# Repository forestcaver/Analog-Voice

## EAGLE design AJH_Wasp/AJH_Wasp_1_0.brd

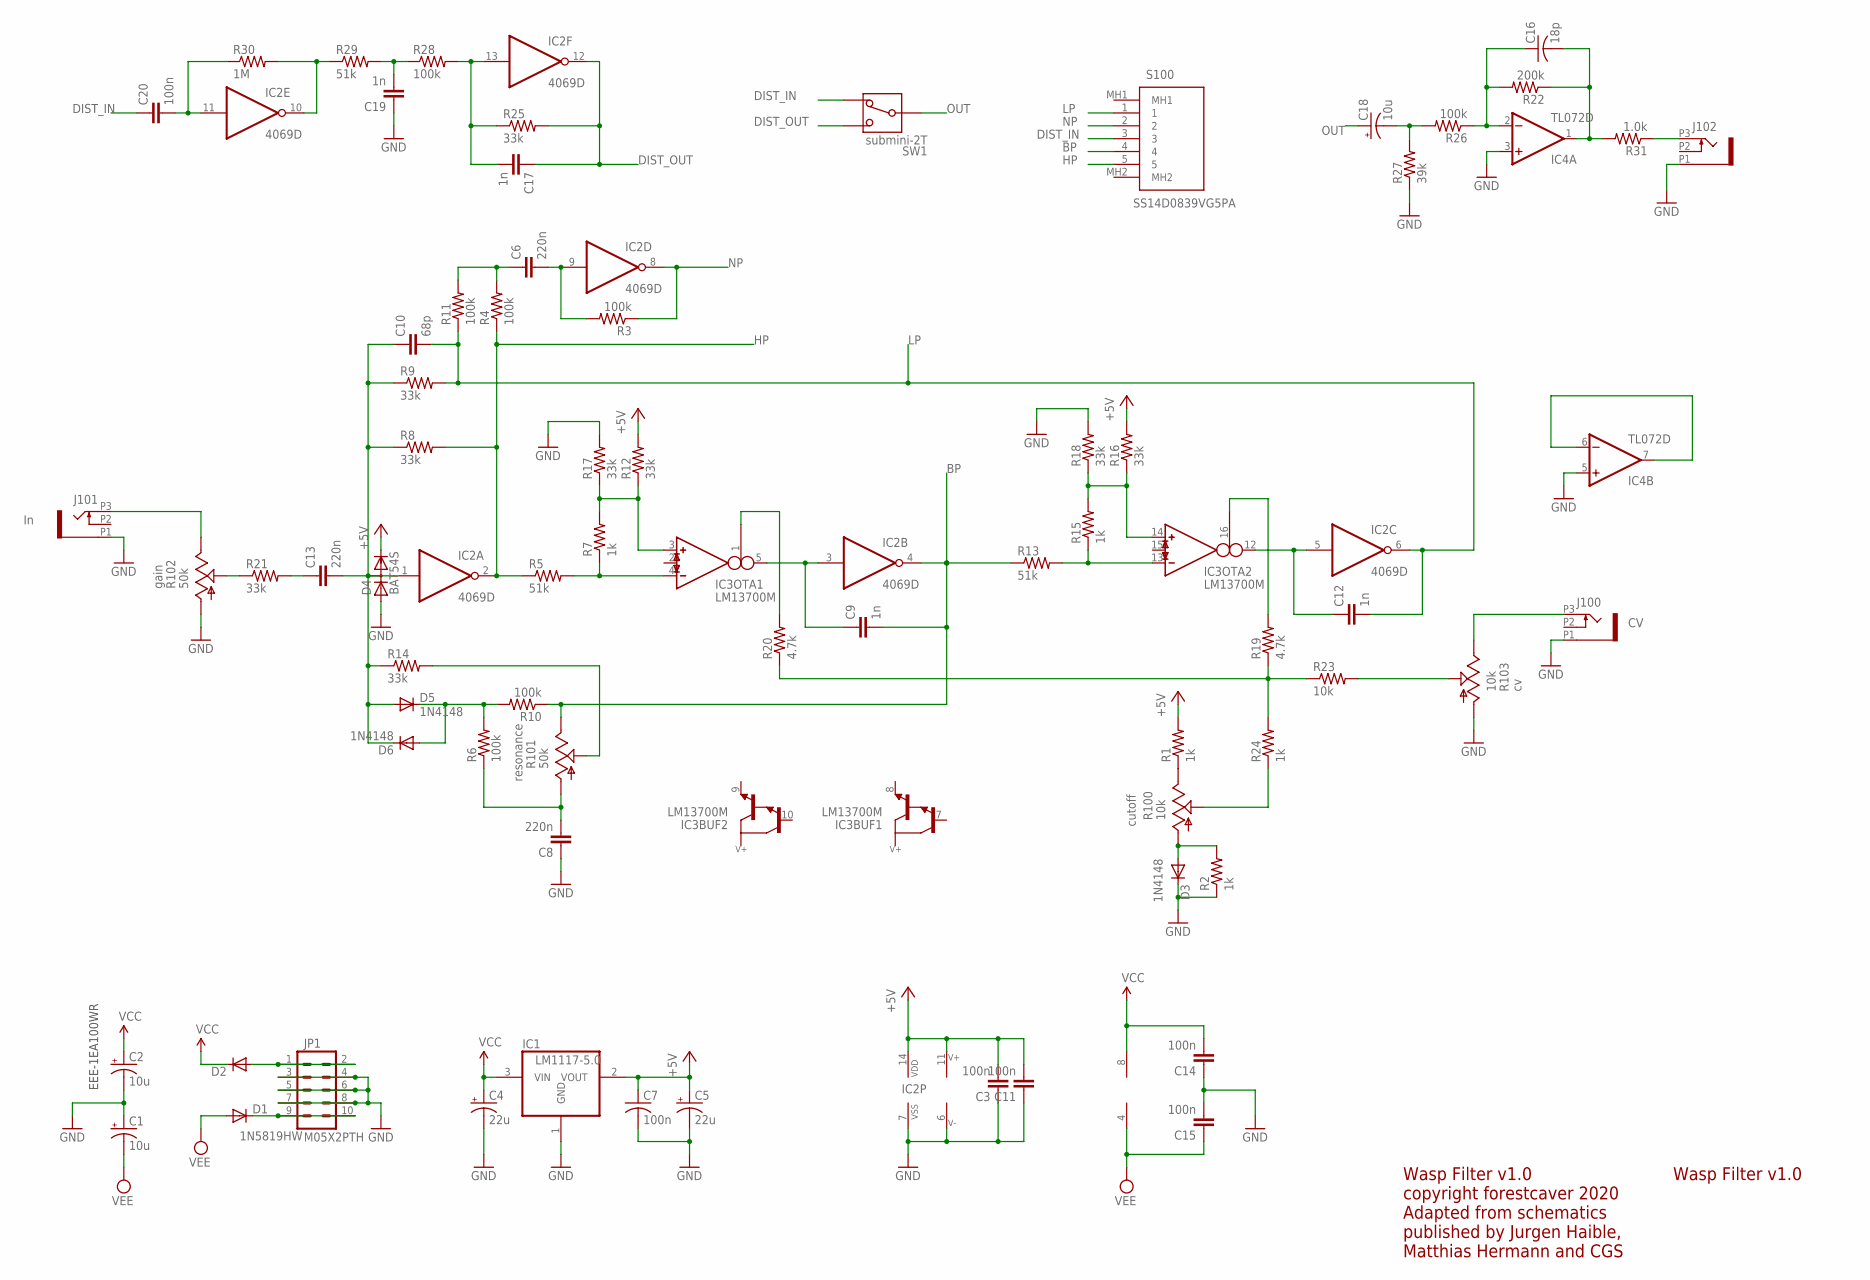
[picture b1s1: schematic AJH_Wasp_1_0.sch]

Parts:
C1, C2, C18: 10u; PANASONIC_B
C3, C7, C11, C14, C15, C20: 100n; C0603
C4, C5: 22u; PANASONIC_C
C6, C8, C13: 220n; C0603
C9, C12, C17, C19: 1n; C0603
C10: 68p; C0603
C16: 18p; C0603
D1, D2: 1N5819HW; SOD123
D3, D5, D6: 1N4148; SOD523
D4: BAT54S; SOT23
IC1: LM1117-5.0; SOT223
IC2: 4069D; SO14
IC3: LM13700M; SO16
IC4: TL072D; SO08
J100, J101: PJ301_THONKICONN8; WQP_PJ_301M8
J102: PJ301_THONKICONN6; WQP_PJ_301M6
JP1: M05X2PTH; AVR_ICSP
R1, R2, R7, R15, R24: 1k; R0603
R3, R4, R6, R10, R11, R26, R28: 100k; R0603
R5, R13, R29: 51k; R0603
R8, R9, R12, R14, R16, R17, R18, R21, R25: 33k; R0603
R19, R20: 4.7k; R0603
R22: 200k; R0603
R23: 10k; R0603
R27: 39k; R0603
R30: 1M; R0603
R31: 1.0k; R0603
R100, R103: 10k; ALPS_POT_VERTICAL_PS
R101, R102: 50k; ALPS_POT_VERTICAL_PS
S100: SS14D0839VG5PA
SW1: submini-2T; SPDT-SUB

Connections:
+5V: C3.2, C5.+, C7.1, C11.2, D4.2 (C), IC1.2 (VOUT), IC2.14 (VDD), IC3.11 (V+), R1.2, R12.2, R16.2
BP: C9.2, IC2.4 (O), R10.1, R13.1, R101.P$1 (E), S100.4
DIST_IN: C20.1, S100.3, SW1.P$3
DIST_OUT: C17.1, IC2.12 (O), R25.2, SW1.P$1
GND: C1.+, C2.-, C3.1, C4.-, C5.-, C7.2, C8.1, C11.1, C14.1, C15.2, C19.1, D3.C, D4.1 (A), IC1.1 (GND), IC2.7 (VSS), IC3.6 (V-), IC4.3 (+IN), IC4.5 (+IN), J100.P1 (1), J101.P1 (1), J102.P1 (1), JP1.3, JP1.4, JP1.5, JP1.6, JP1.7, JP1.8, R2.1, R17.2, R18.2, R27.1, R102.P$3 (A), R103.P$3 (A)
HP: IC2.2 (O), R4.1, R5.1, R8.2, S100.5
LP: C10.2, C12.2, IC2.6 (O), R9.2, R11.1, S100.1
unnamed: J101.P3 (3), R102.P$1 (E)
unnamed: R21.1, R102.P$2 (S)
unnamed: C13.1, R21.2
unnamed: C10.1, C13.2, D4.3 (AC), D5.A, D6.C, IC2.1 (I), R8.1, R9.1, R14.1
unnamed: IC3.14 (IN_P), R15.2, R16.1, R18.1
unnamed: D2.A, JP1.1, JP1.2
unnamed: IC3.1 (I_BIAS), R20.2
unnamed: C6.2, IC2.9 (I), R3.2
unnamed: C6.1, R4.2, R11.2
unnamed: D5.C, D6.A, R6.2, R10.2
unnamed: IC3.13 (IN_N), R13.2, R15.1
unnamed: C8.2, R6.1, R101.P$3 (A)
unnamed: R14.2, R101.P$2 (S)
unnamed: IC3.3 (IN_P), R7.2, R12.1, R17.1
unnamed: IC3.4 (IN_N), R5.2, R7.1
unnamed: C9.1, IC2.3 (I), IC3.5 (OUT)
unnamed: IC3.16 (I_BIAS), R19.2
unnamed: R19.1, R20.1, R23.1, R24.2
unnamed: C12.1, IC2.5 (I), IC3.12 (OUT)
unnamed: D1.C, JP1.9, JP1.10
unnamed: R23.2, R103.P$2 (S)
unnamed: R1.1, R100.P$1 (E)
unnamed: D3.A, R2.2, R100.P$3 (A)
unnamed: R24.1, R100.P$2 (S)
unnamed: C20.2, IC2.11 (I), R30.1
unnamed: IC2.10 (O), R29.1, R30.2
unnamed: C19.2, R28.1, R29.2
unnamed: C17.2, IC2.13 (I), R25.1, R28.2
unnamed: J100.P3 (3), R103.P$1 (E)
unnamed: IC4.6 (-IN), IC4.7 (OUT)
unnamed: C18.-, R26.2, R27.2
unnamed: C16.1, IC4.2 (-IN), R22.2, R26.1
unnamed: C16.2, IC4.1 (OUT), R22.1, R31.2
NP: IC2.8 (O), R3.1, S100.2
OUT: C18.+, SW1.P$2
ROUT_JACK1: J102.P3 (3), R31.1
VCC: C2.+, C4.+, C14.2, D2.C, IC1.3 (VIN), IC4.8 (V+)
VEE: C1.-, C15.1, D1.A, IC4.4 (V-)

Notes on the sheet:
EEE-1EA100WR
Wasp Filter v1.0
Wasp Filter v1.0 copyright forestcaver 2020 Adapted from schematics published by Jurgen Haible, Matthias Hermann and CGS

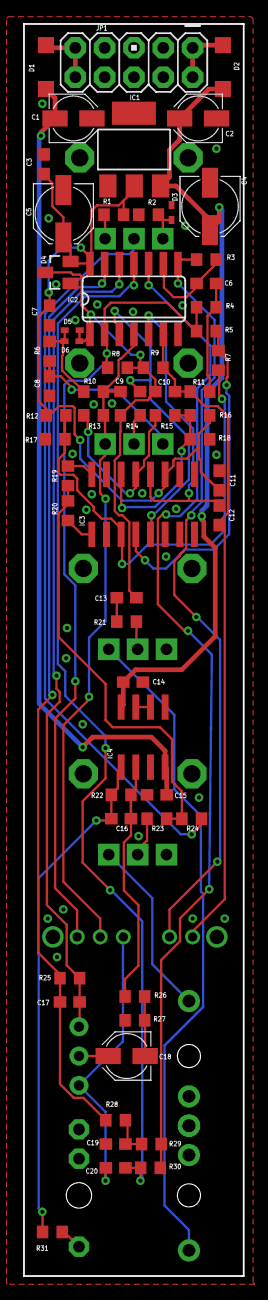
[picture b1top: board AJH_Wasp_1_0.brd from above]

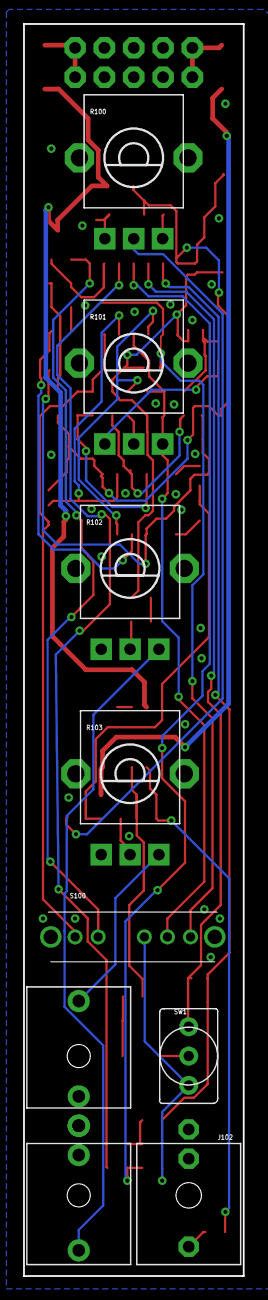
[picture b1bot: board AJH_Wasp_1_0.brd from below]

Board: 2 copper layers, 19.0 x 108.4 mm, 71 parts (9 on the bottom side), 45 nets.

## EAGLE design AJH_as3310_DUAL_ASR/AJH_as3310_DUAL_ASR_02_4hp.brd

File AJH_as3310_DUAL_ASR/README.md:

# Dual ASR

Built and tested 

CC-BY-NC-SA 4.0

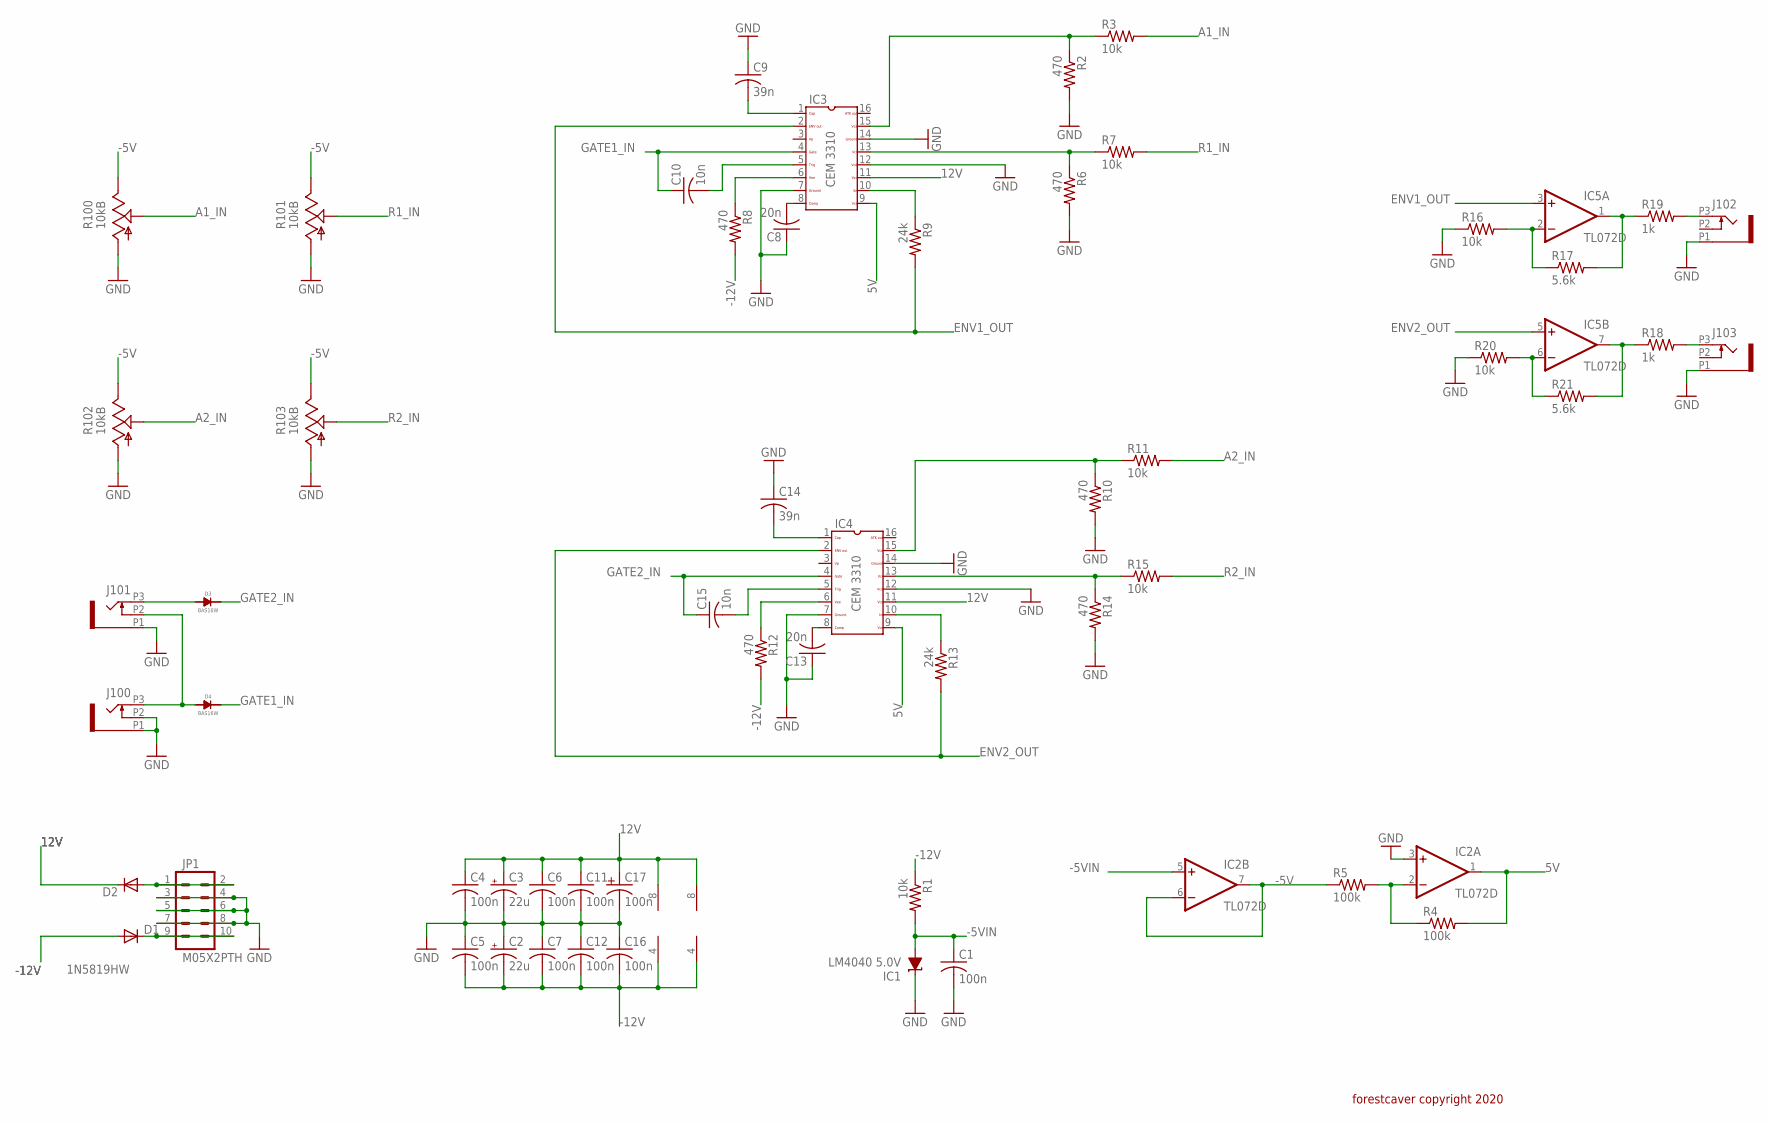
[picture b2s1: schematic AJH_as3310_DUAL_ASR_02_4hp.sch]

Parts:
C1, C4, C5, C6, C7, C11, C12, C16, C17: 100n; C0603
C2, C3: 22u; PANASONIC_B
C8, C13: 20n; C0603
C9, C14: 39n; C0603
C10, C15: 10n; C0603
D1, D2: 1N5819HW; SOD123
D3, D4: BAS16W; SOT-323
IC1: LM4040 5.0V; DBZ_R-PDSO-G3
IC2, IC5: TL072D; SO08
IC3, IC4: CEM3310SOIC16; SO16
J100, J101, J102, J103: PJ301_THONKICONN6; WQP_PJ_301M6
JP1: M05X2PTH; AVR_ICSP
R1, R3, R7, R11, R15, R16, R20: 10k; R0603
R2, R6, R8, R10, R12, R14: 470; R0603
R4, R5: 100k; R0603
R9, R13: 24k; R0603
R17, R21: 5.6k; R0603
R18, R19: 1k; R0603
R100, R101, R102, R103: 10kB; ALPS_POT_VERTICAL

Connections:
5V: IC2.1 (OUT), IC3.9, IC4.9, R4.2
12V: C3.+, C4.1, C6.1, C11.1, C17.1, D2.C, IC2.8 (V+), IC3.11, IC4.11, IC5.8 (V+)
-5V: IC2.6 (-IN), IC2.7 (OUT), R5.1, R100.P$1 (E), R101.P$1 (E), R102.P$1 (E), R103.P$1 (E)
-5VIN: C1.1, IC1.2 (A), IC2.5 (+IN), R1.2
-12V: C2.-, C5.2, C7.2, C12.2, C16.2, D1.A, IC2.4 (V-), IC5.4 (V-), R1.1, R8.2, R12.2
A1_IN: R3.2, R100.P$2 (S)
A2_IN: R11.2, R102.P$2 (S)
ENV1_OUT: IC3.2, IC5.3 (+IN), R9.2
ENV2_OUT: IC4.2, IC5.5 (+IN), R13.2
GATE1_IN: C10.1, D4.CATHODE, IC3.4
GATE2_IN: C15.1, D3.CATHODE, IC4.4
GND: C1.2, C2.+, C3.-, C4.2, C5.1, C6.2, C7.1, C8.1, C9.1, C11.2, C12.1, C13.1, C14.1, C16.1, C17.2, IC1.1 (C), IC2.3 (+IN), IC3.7, IC3.12, IC3.14, IC4.7, IC4.12, IC4.14, J100.P1 (1), J100.P2 (2), J101.P1 (1), J102.P1 (1), J103.P1 (1), JP1.3, JP1.4, JP1.5, JP1.6, JP1.7, JP1.8, R2.2, R6.2, R10.2, R14.2, R16.1, R20.1, R100.P$3 (A), R101.P$3 (A), R102.P$3 (A), R103.P$3 (A)
unnamed: D3.ANODE, J101.P3 (3)
unnamed: C15.2, IC4.5
unnamed: C9.2, IC3.1
unnamed: C8.2, IC3.8
unnamed: C10.2, IC3.5
unnamed: D2.A, JP1.1, JP1.2
unnamed: IC3.13, R6.1, R7.1
unnamed: IC3.6, R8.1
unnamed: C13.2, IC4.8
unnamed: IC3.10, R9.1
unnamed: IC4.6, R12.1
unnamed: IC3.15, R2.1, R3.1
unnamed: IC2.2 (-IN), R4.1, R5.2
unnamed: C14.2, IC4.1
unnamed: IC4.10, R13.1
unnamed: IC4.13, R14.1, R15.1
unnamed: IC4.15, R10.1, R11.1
unnamed: IC5.6 (-IN), R20.2, R21.1
unnamed: IC5.7 (OUT), R18.1, R21.2
unnamed: D1.C, JP1.9, JP1.10
unnamed: IC5.2 (-IN), R16.2, R17.1
unnamed: IC5.1 (OUT), R17.2, R19.1
unnamed: J102.P3 (3), R19.2
unnamed: J103.P3 (3), R18.2
unnamed: D4.ANODE, J100.P3 (3), J101.P2 (2)
R1_IN: R7.2, R101.P$2 (S)
R2_IN: R15.2, R103.P$2 (S)

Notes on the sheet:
forestcaver copyright 2020

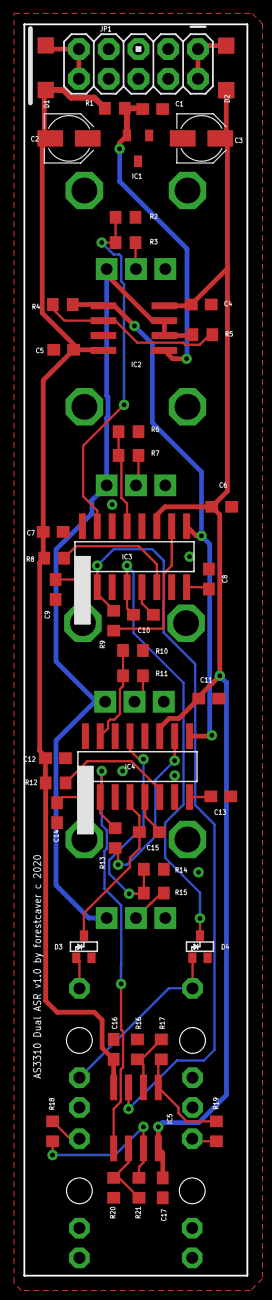
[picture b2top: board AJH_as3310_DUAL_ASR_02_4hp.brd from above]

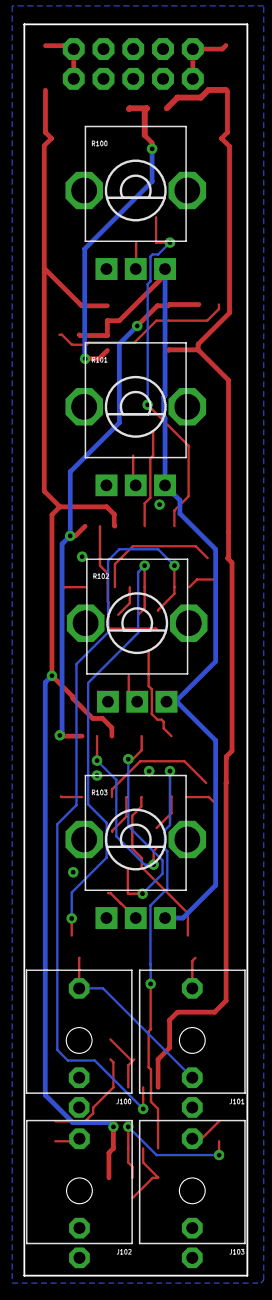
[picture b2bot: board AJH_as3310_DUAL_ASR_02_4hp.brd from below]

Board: 2 copper layers, 19.0 x 106.8 mm, 56 parts (8 on the bottom side), 39 nets.

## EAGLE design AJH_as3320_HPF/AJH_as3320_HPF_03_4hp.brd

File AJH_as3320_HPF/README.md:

# 3320 HPF

Built and tested

CC-BY-NC-SA 4.0

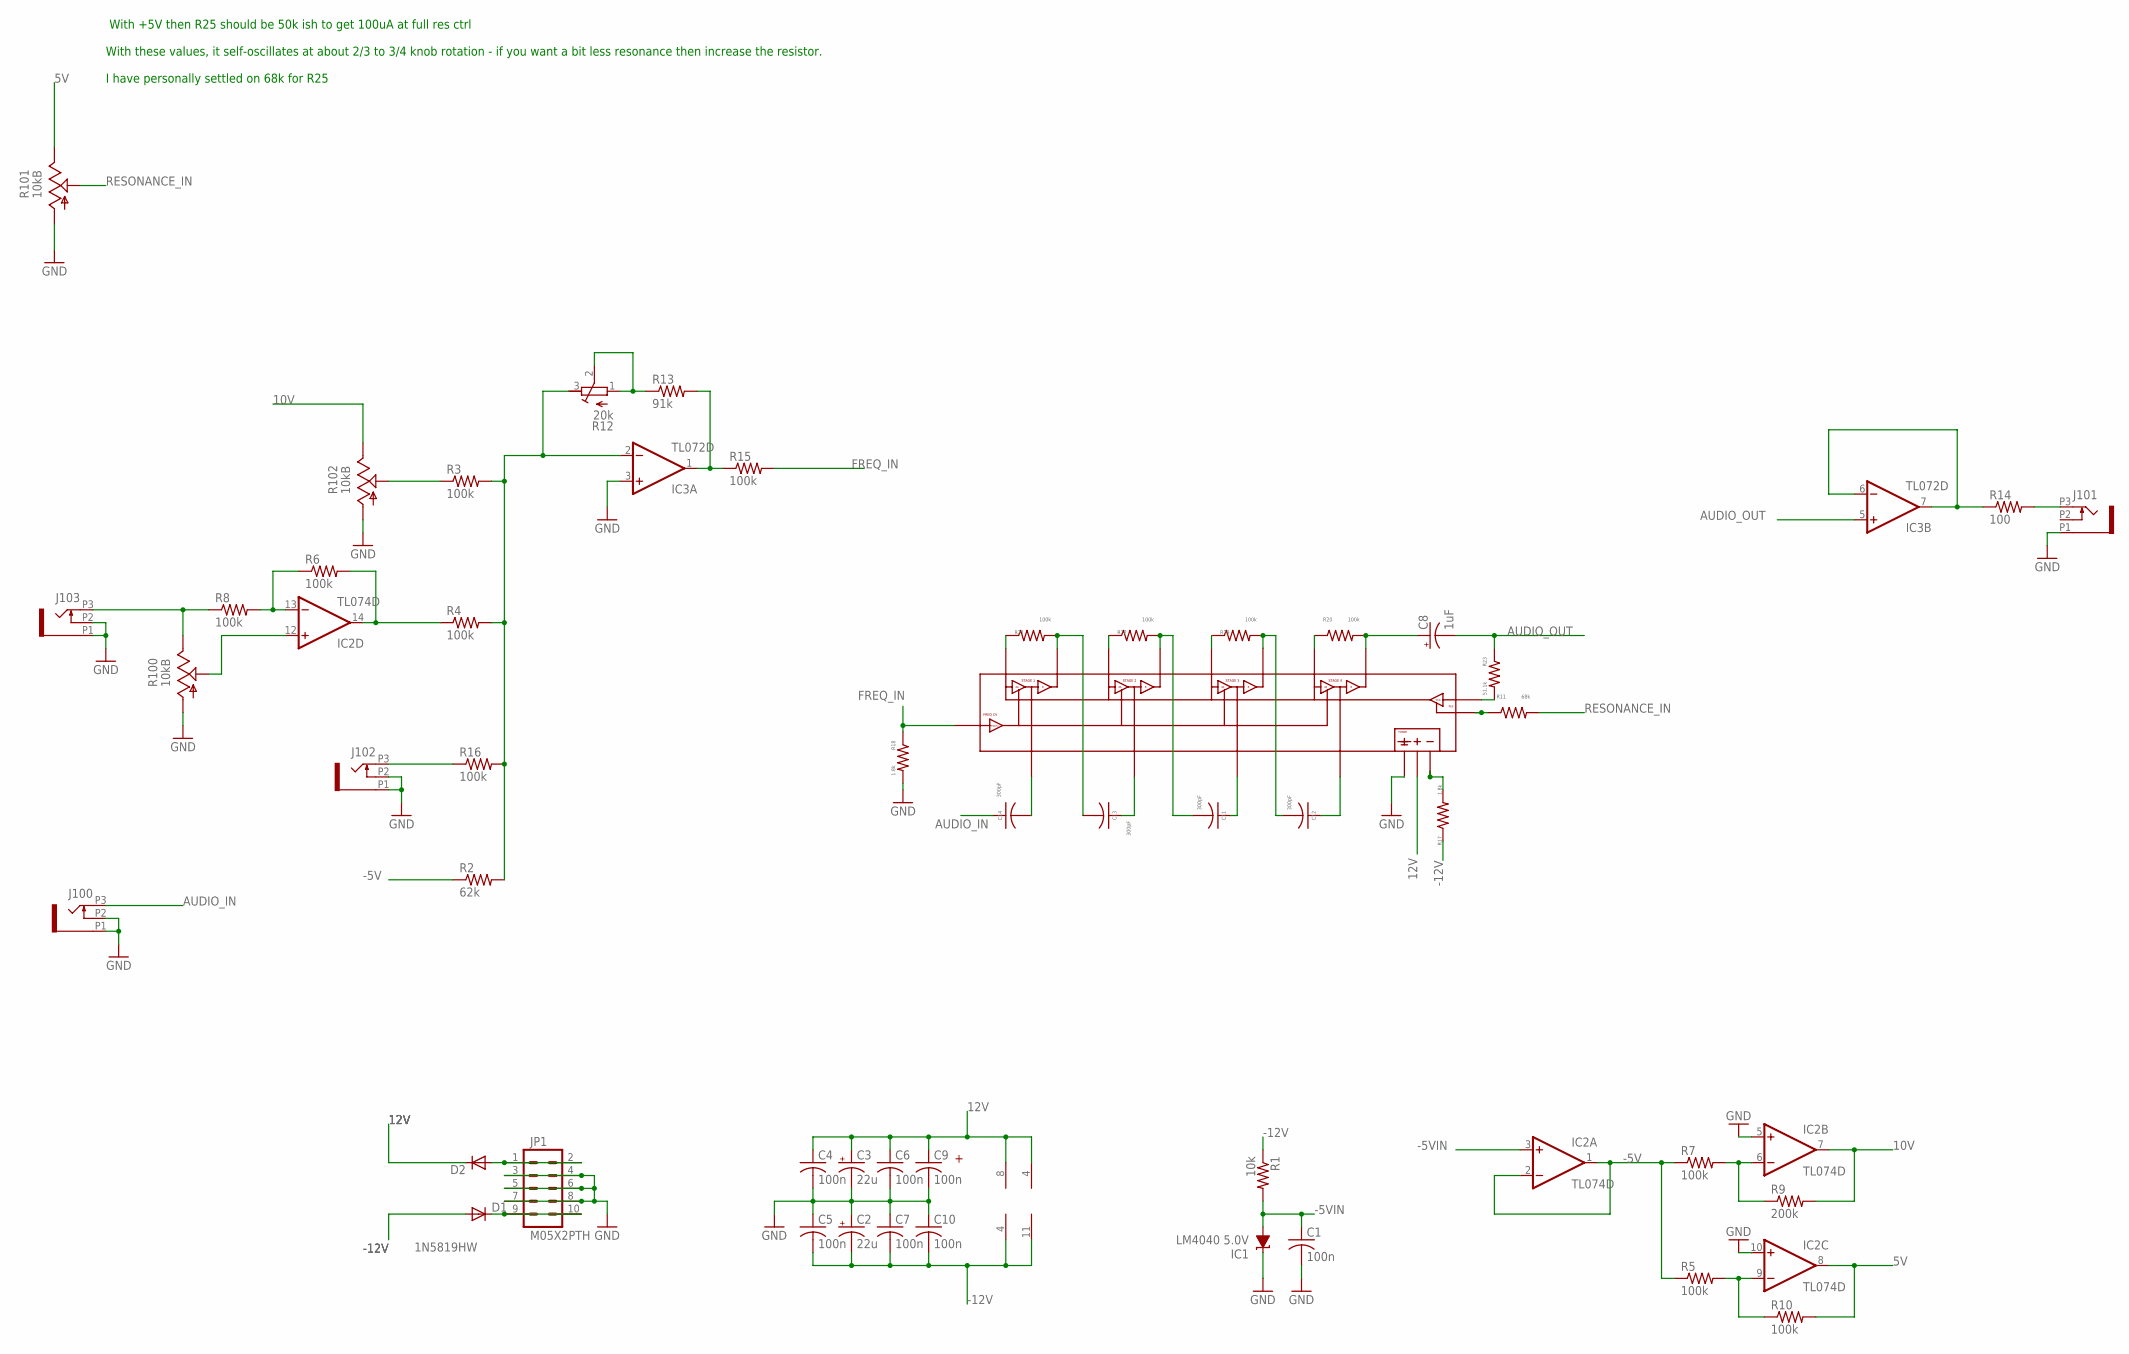
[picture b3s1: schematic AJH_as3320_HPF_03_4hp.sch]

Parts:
C1, C4, C5, C6, C7, C9, C10: 100n; C0603
C2, C3: 22u; PANASONIC_B
C8: 1uF; PANASONIC_B
C11, C12, C13, C14: 300pF; C0603
D1, D2: 1N5819HW; SOD123
IC1: LM4040 5.0V; DBZ_R-PDSO-G3
IC2: TL074D; SO14
IC3: TL072D; SO08
IC4: CEM3320_UNFOLDEDQFN; QFN24
J100, J101, J102, J103: PJ301_THONKICONN6; WQP_PJ_301M6
JP1: M05X2PTH; AVR_ICSP
R1: 10k; R0603
R2: 62k; R0603
R3, R4, R5, R6, R7, R8, R10, R15, R16, R19, R20, R21, R22: 100k; R0603
R9: 200k; R0603
R11: 68k; R0603
R12: 20k; RTRIM3296X
R13: 91k; R0603
R14: 100; R0603
R17, R18: 1.8k; R0603
R23: 51.1k; R0603
R100, R101, R102: 10kB; ALPS_POT_VERTICAL

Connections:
5V: IC2.8 (OUT), R10.2, R101.P$1 (E)
10V: IC2.7 (OUT), R9.2, R102.P$1 (E)
12V: C3.+, C4.1, C6.1, C9.1, D2.C, IC2.4 (V+), IC3.8 (V+), IC4.P$22 (POSRAIL)
-5V: IC2.1 (OUT), IC2.2 (-IN), R2.1, R5.1, R7.1
-5VIN: C1.1, IC1.2 (A), IC2.3 (+IN), R1.2
-12V: C2.-, C5.2, C7.2, C10.2, D1.A, IC2.11 (V-), IC3.4 (V-), R1.1, R17.1
AUDIO_IN: C14.1, J100.P3 (3)
AUDIO_OUT: C8.-, IC3.5 (+IN), R23.1
FREQ_IN: IC4.P$19 (FREQCV), R15.2, R18.1
GND: C1.2, C2.+, C3.-, C4.2, C5.1, C6.2, C7.1, C9.2, C10.1, IC1.1 (C), IC2.5 (+IN), IC2.10 (+IN), IC3.3 (+IN), IC4.P$7 (GROUND), J100.P1 (1), J100.P2 (2), J101.P1 (1), J102.P1 (1), J102.P2 (2), J103.P1 (1), J103.P2 (2), JP1.3, JP1.4, JP1.5, JP1.6, JP1.7, JP1.8, R18.2, R100.P$3 (A), R101.P$3 (A), R102.P$3 (A)
unnamed: IC3.6 (-IN), IC3.7 (OUT), R14.1
unnamed: IC2.12 (+IN), R100.P$2 (S)
unnamed: R3.1, R102.P$2 (S)
unnamed: IC2.13 (-IN), R6.1, R8.2
unnamed: D2.A, JP1.1, JP1.2
unnamed: IC3.2 (-IN), R2.2, R3.2, R4.2, R12.3 (A), R16.2
unnamed: IC3.1 (OUT), R13.2, R15.1
unnamed: J102.P3 (3), R16.1
unnamed: J101.P3 (3), R14.2
unnamed: IC2.14 (OUT), R4.1, R6.2
unnamed: IC2.9 (-IN), R5.2, R10.1
unnamed: IC4.P$14 (FEEDBACK_IN), R23.2
unnamed: IC2.6 (-IN), R7.2, R9.1
unnamed: D1.C, JP1.9, JP1.10
unnamed: R12.1 (E), R12.2 (S), R13.1
unnamed: J103.P3 (3), R8.1, R100.P$1 (E)
unnamed: IC4.P$20 (NEGRAIL), R17.2
unnamed: IC4.P$15 (RESONANCE_CV), R11.1
unnamed: C14.2, IC4.P$9 (STAGE1_CAP)
unnamed: IC4.P$4 (STAGE1_IN), R21.1
unnamed: C13.2, IC4.P$12 (STAGE1_OUT), R21.2
unnamed: C13.1, IC4.P$8 (STAGE2_CAP)
unnamed: IC4.P$5 (STAGE2_IN), R22.1
unnamed: C11.2, IC4.P$11 (STAGE2_OUT), R22.2
unnamed: C11.1, IC4.P$24 (STAGE3_CAP)
unnamed: IC4.P$2 (STAGE3_IN), R19.1
unnamed: C12.2, IC4.P$23 (STAGE3_OUT), R19.2
unnamed: C12.1, IC4.P$17 (STAGE4_CAP)
unnamed: IC4.P$3 (STAGE4_IN), R20.1
unnamed: C8.+, IC4.P$16 (STAGE4_OUT), R20.2
RESONANCE_IN: R11.2, R101.P$2 (S)

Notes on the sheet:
With +5V then R25 should be 50k ish to get 100uA at full res ctrl With these values, it self-oscillates at about 2/3 to 3/4 knob rotation - if you want a bit less resonance then increase the resistor. I have personally settled on 68k for R25

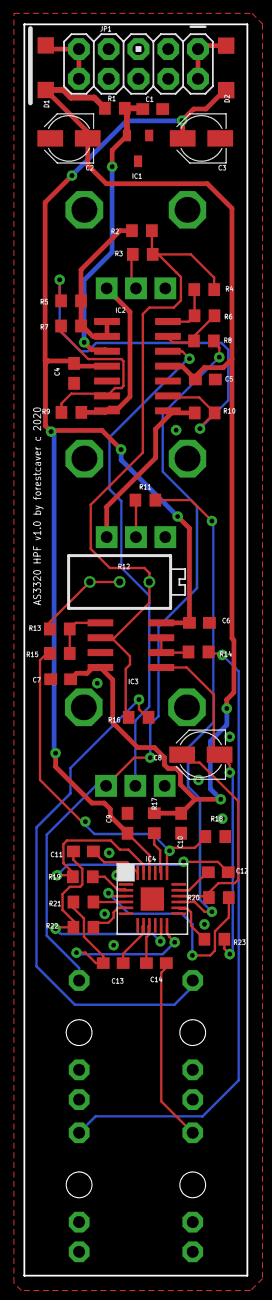
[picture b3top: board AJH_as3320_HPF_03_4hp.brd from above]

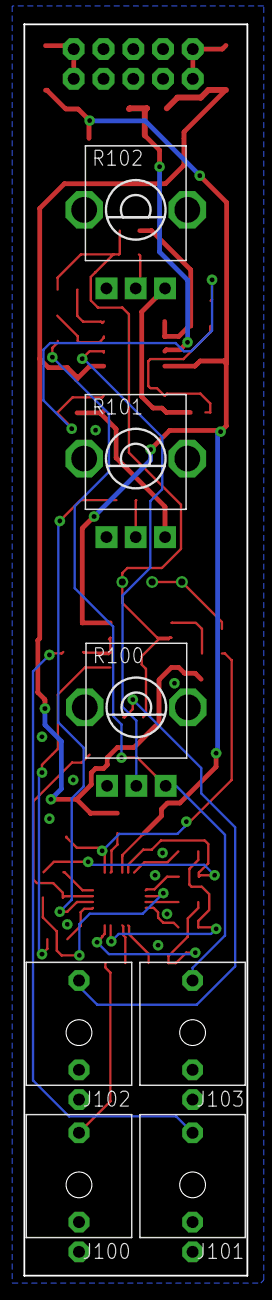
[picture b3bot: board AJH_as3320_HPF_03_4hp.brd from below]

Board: 2 copper layers, 19.0 x 106.8 mm, 51 parts (7 on the bottom side), 41 nets.
